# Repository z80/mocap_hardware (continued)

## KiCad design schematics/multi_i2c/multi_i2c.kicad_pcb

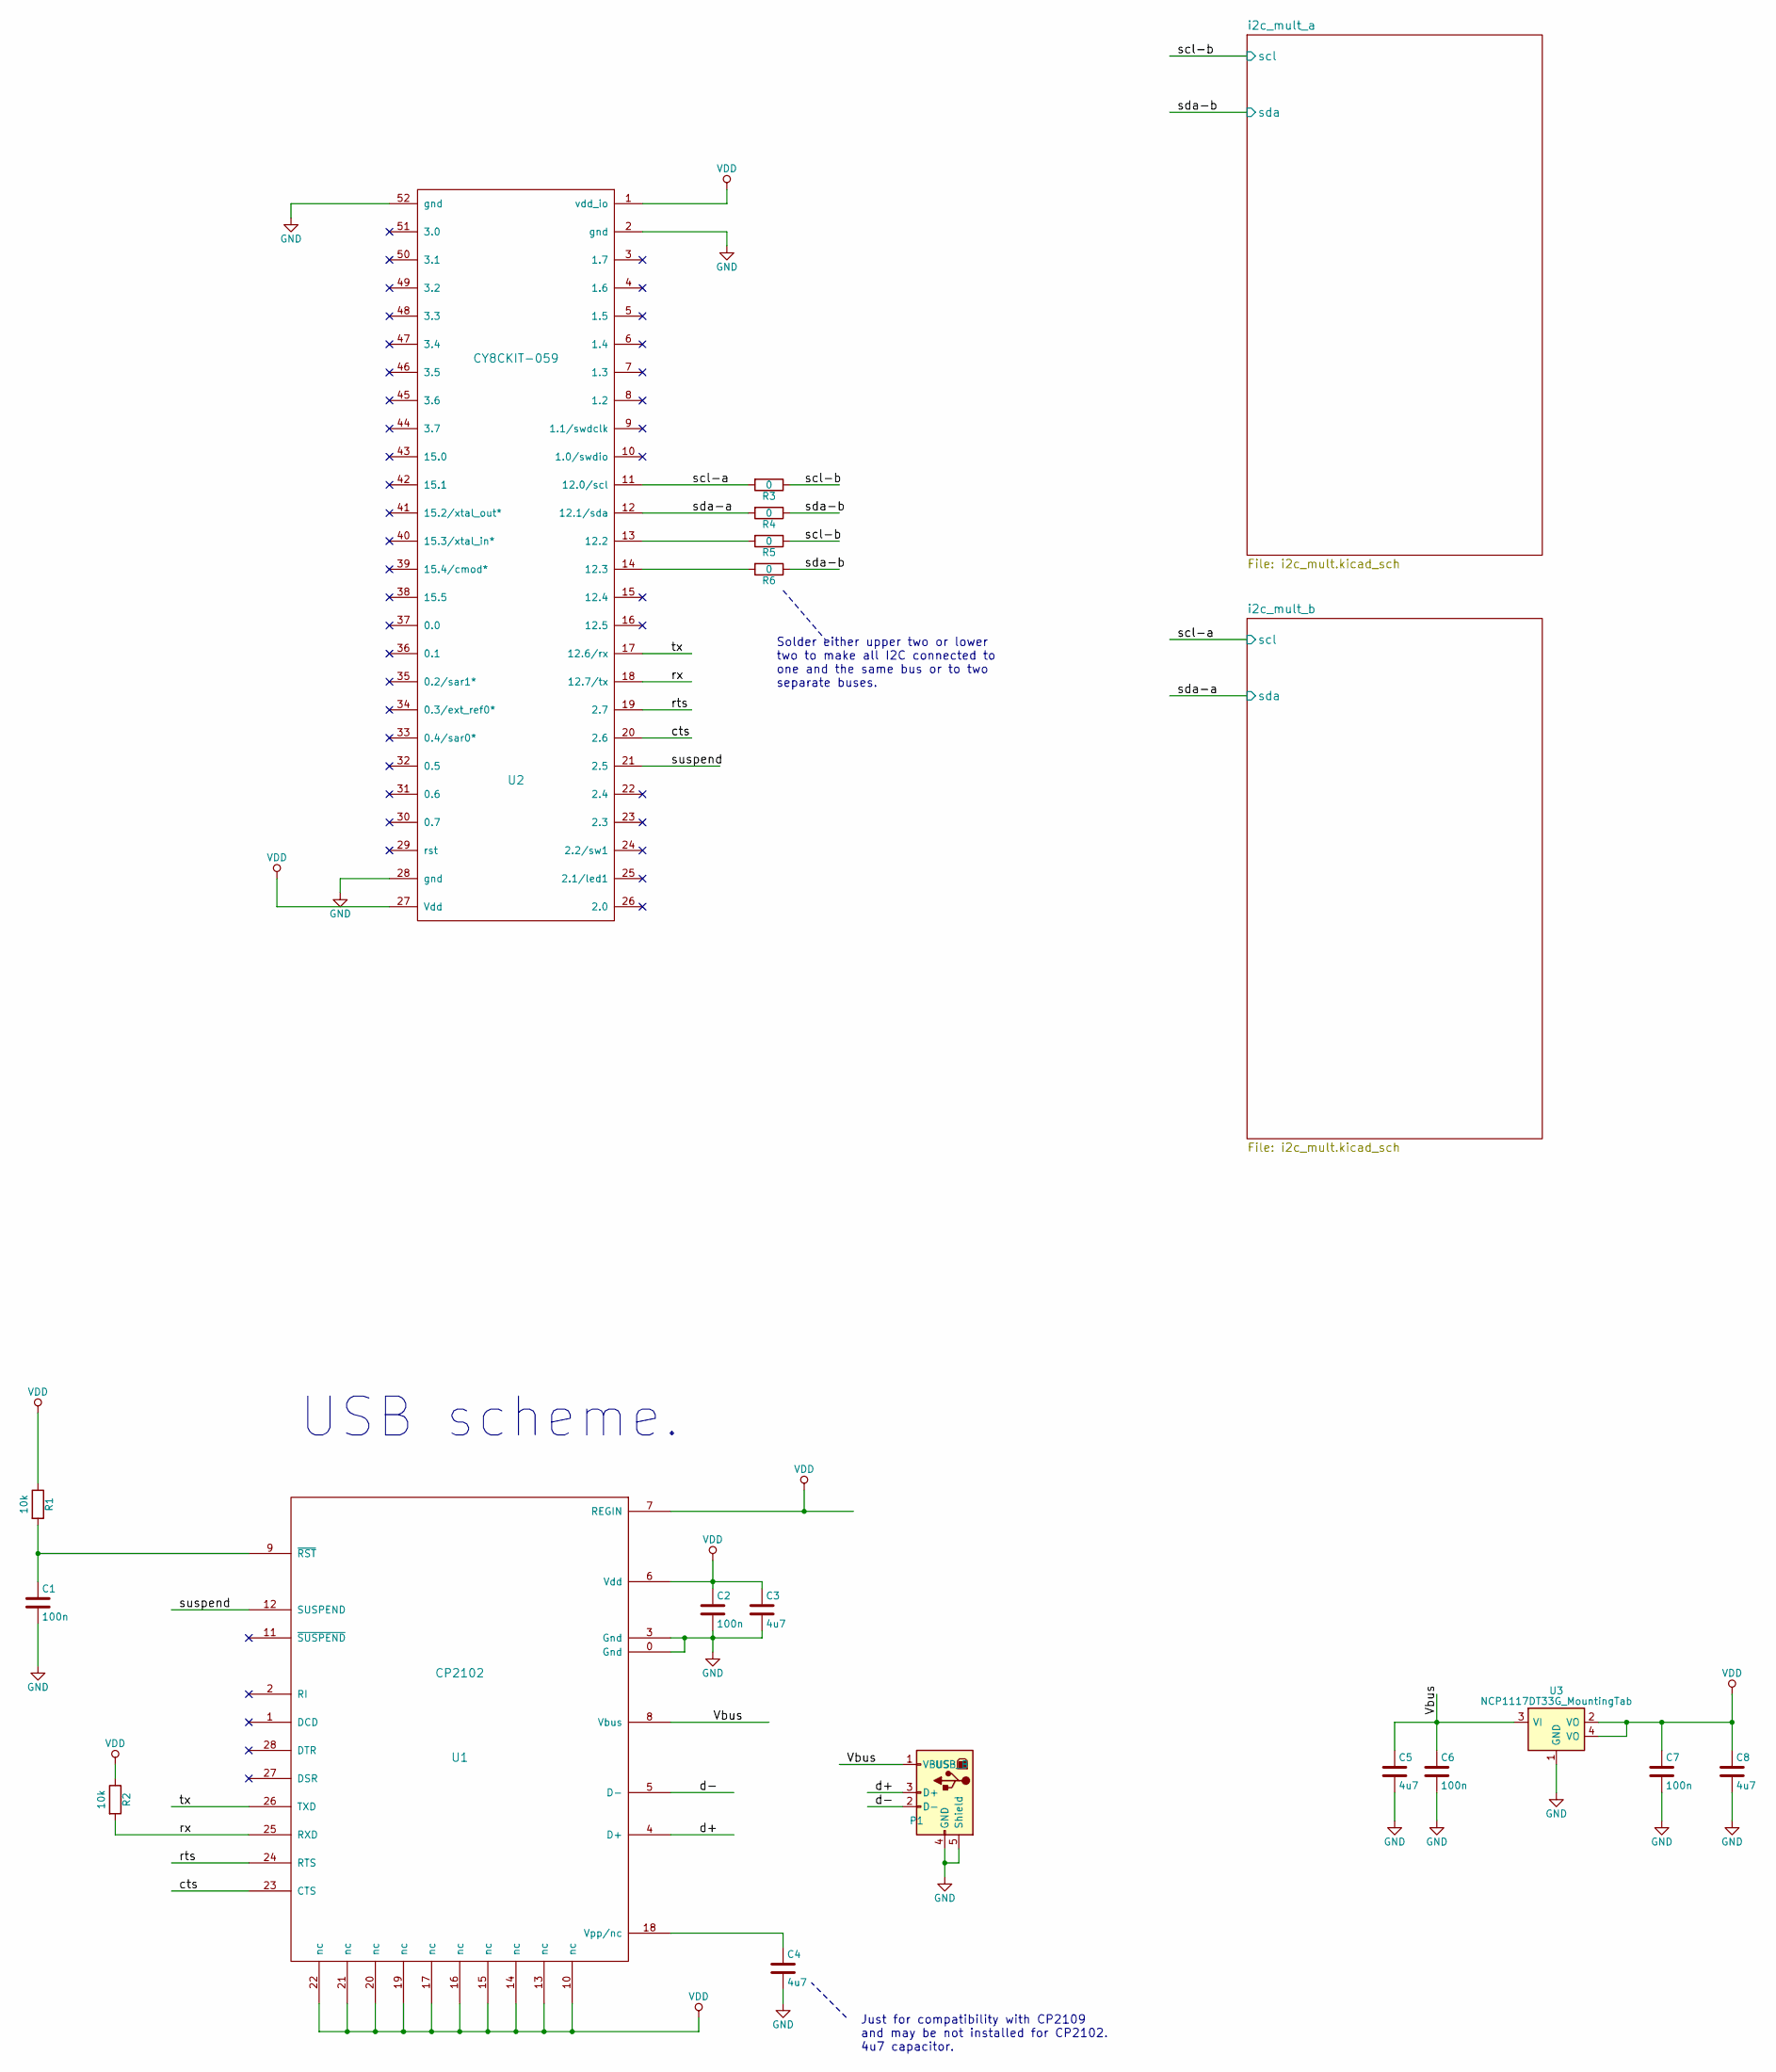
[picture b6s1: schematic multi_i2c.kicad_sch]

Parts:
C1, C2, C6, C7: 100n; C_0603
C3, C4, C5, C8: 4u7; C_0603
P1: USB_B
R1, R2: 10k; R_0603
R3, R4, R5, R6: 0; R_0603
U1: CP2102
U2: CY8CKIT-059; cy8ckit-059
U3: NCP1117DT33G_MountingTab; SOT-223

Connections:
/Vbus: C5.1, C6.1, P1.1 (VBUS), U1.8 (Vbus), U3.3 (VI)
/cts: U1.23 (CTS), U2.20 (2.6)
/d+: P1.3 (D+), U1.4 (D+)
/d-: P1.2 (D-), U1.5 (D-)
/rts: U1.24 (RTS), U2.19 (2.7)
/rx: R2.2, U1.25 (RXD), U2.18 (12.7/tx)
/scl-a: R3.2, U2.11 (12.0/scl); also elsewhere on the board
/scl-b: R3.1, R5.1; also elsewhere on the board
/sda-a: R4.2, U2.12 (12.1/sda); also elsewhere on the board
/sda-b: R4.1, R6.1; also elsewhere on the board
/suspend: U1.12 (SUSPEND), U2.21 (2.5)
/tx: U1.26 (TXD), U2.17 (12.6/rx)
GND: C1.2, C2.2, C3.2, C4.2, C5.2, C6.2, C7.2, C8.2, P1.4 (GND), P1.5 (Shield), U1.0 (Gnd), U1.3 (Gnd), U2.2 (gnd), U2.28 (gnd), U2.52 (gnd), U3.1 (GND); also elsewhere on the board
unnamed: C1.1, R1.2, U1.9 (~RST)
unnamed: C4.1, U1.18 (Vpp/nc)
unnamed: R5.2, U2.13 (12.2)
unnamed: R6.2, U2.14 (12.3)
VDD: C2.1, C3.1, C7.1, C8.1, R1.1, R2.1, U1.6 (Vdd), U1.7 (REGIN), U1.10 (nc), U1.13 (nc), U1.14 (nc), U1.15 (nc), U1.16 (nc), U1.17 (nc), U1.19 (nc), U1.20 (nc), U1.21 (nc), U1.22 (nc), U2.1 (vdd_io), U2.27 (Vdd), U3.2 (VO), U3.4 (VO); also elsewhere on the board

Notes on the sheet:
USB scheme.
Solder either upper two or lower two to make all I2C connected to one and the same bus or to two separate buses.
Just for compatibility with CP2109 and may be not installed for CP2102. 4u7 capacitor.

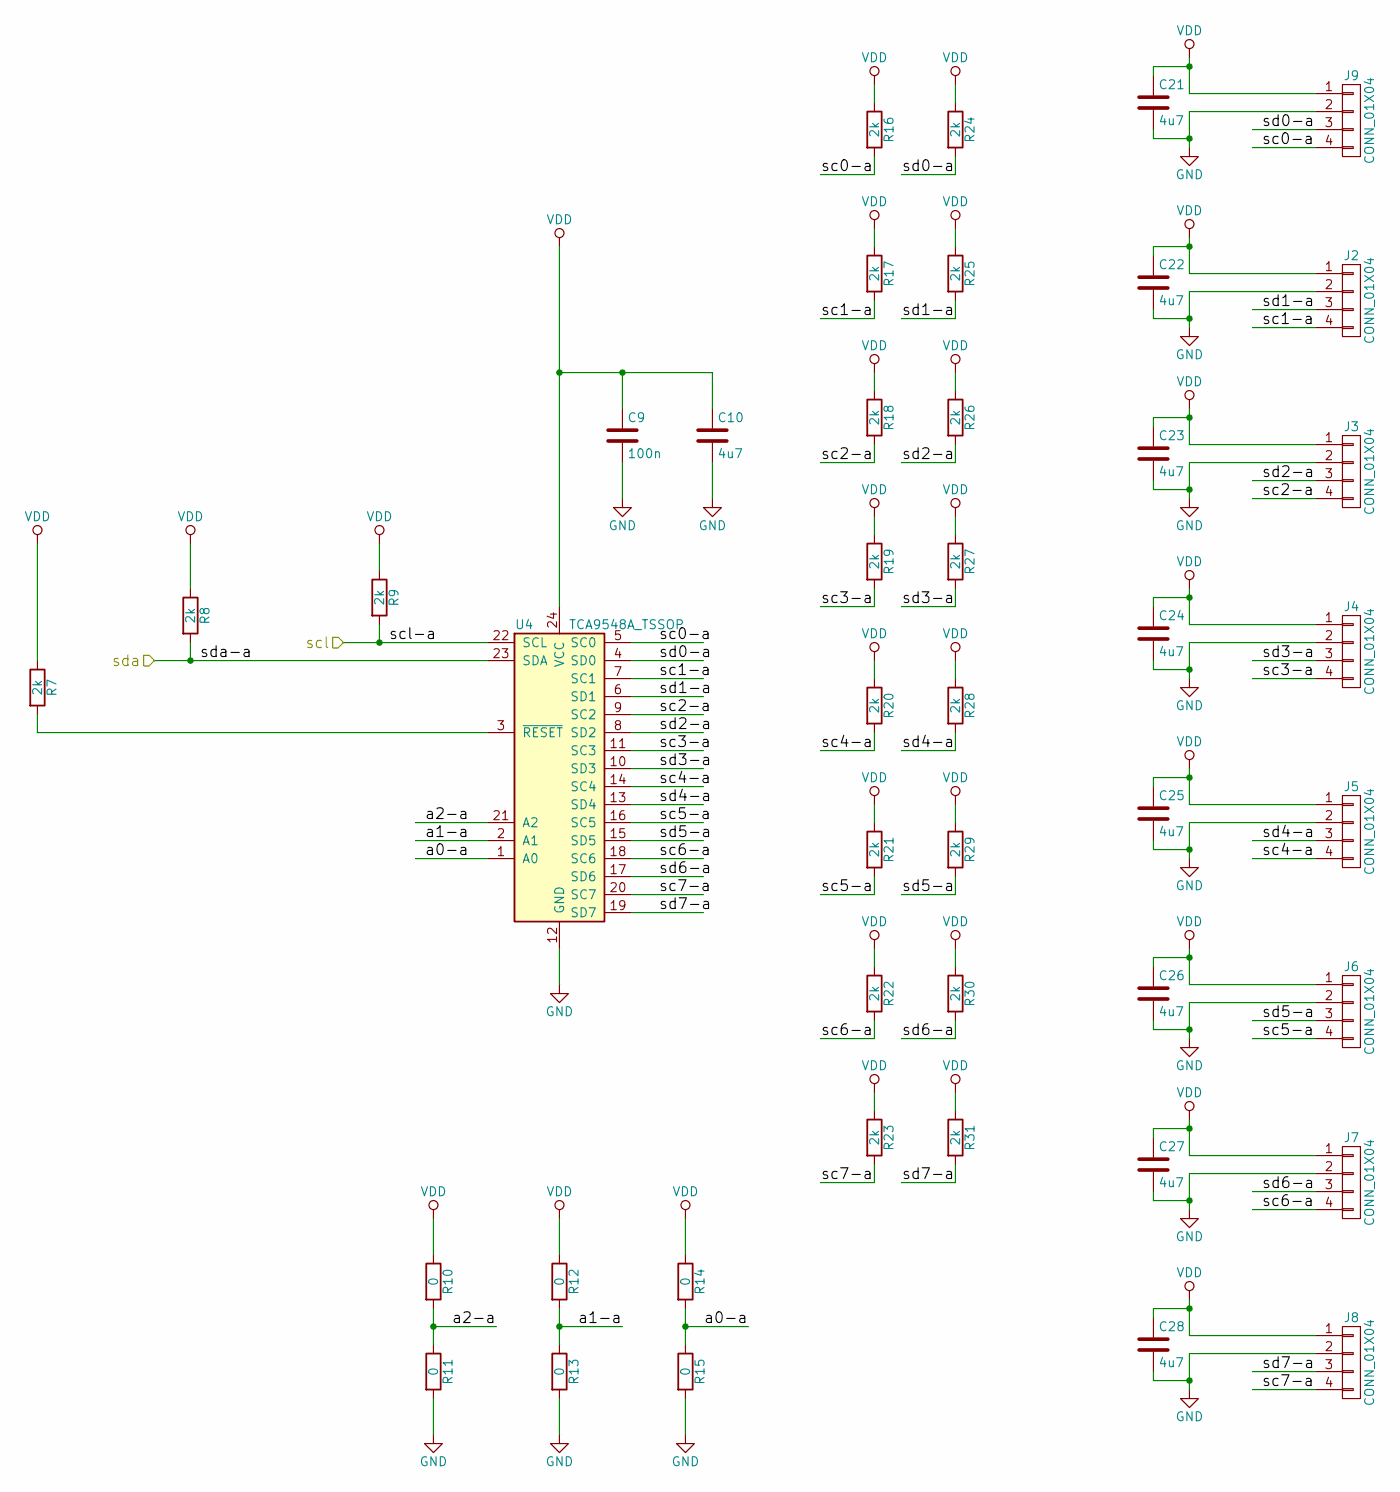
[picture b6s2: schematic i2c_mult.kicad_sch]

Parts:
C9: 100n; C_0603
C10, C21, C22, C23, C24, C25, C26, C27, C28: 4u7; C_0603
J2, J3, J4, J5, J6, J7, J8, J9: CONN_01X04; Pin_Header_Straight_1x04_Pitch1.27mm
R7, R8, R9, R16, R17, R18, R19, R20, R21, R22, R23, R24, R25, R26, R27, R28, R29, R30, R31: 2k; R_0603
R10, R11, R12, R13, R14, R15: 0; R_0603
U4: TCA9548A_TSSOP; TSSOP-24_4.4x7.8mm_Pitch0.65mm

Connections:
/i2c_mult_a/a0-a: R14.2, R15.1, U4.1 (A0)
/i2c_mult_a/a1-a: R12.2, R13.1, U4.2 (A1)
/i2c_mult_a/a2-a: R10.2, R11.1, U4.21 (A2)
/i2c_mult_a/sc1-a: J2.4, R17.2, U4.7 (SC1)
/i2c_mult_a/sc2-a: J3.4, R18.2, U4.9 (SC2)
/i2c_mult_a/sc3-a: J4.4, R19.2, U4.11 (SC3)
/i2c_mult_a/sc4-a: J5.4, R20.2, U4.14 (SC4)
/i2c_mult_a/sc5-a: J6.4, R21.2, U4.16 (SC5)
/i2c_mult_a/sc6-a: J7.4, R22.2, U4.18 (SC6)
/i2c_mult_a/sc7-a: J8.4, R23.2, U4.20 (SC7)
/i2c_mult_a/sd1-a: J2.3, R25.2, U4.6 (SD1)
/i2c_mult_a/sd2-a: J3.3, R26.2, U4.8 (SD2)
/i2c_mult_a/sd3-a: J4.3, R27.2, U4.10 (SD3)
/i2c_mult_a/sd4-a: J5.3, R28.2, U4.13 (SD4)
/i2c_mult_a/sd5-a: J6.3, R29.2, U4.15 (SD5)
/i2c_mult_a/sd6-a: J7.3, R30.2, U4.17 (SD6)
/i2c_mult_a/sd7-a: J8.3, R31.2, U4.19 (SD7)
/scl-b: R9.2, U4.22 (SCL); also elsewhere on the board
/sda-b: R8.2, U4.23 (SDA); also elsewhere on the board
GND: C9.2, C10.2, C21.2, C22.2, C23.2, C24.2, C25.2, C26.2, C27.2, C28.2, J2.2, J3.2, J4.2, J5.2, J6.2, J7.2, J8.2, J9.2, R11.2, R13.2, R15.2, U4.12 (GND); also elsewhere on the board
unnamed: R7.2, U4.3 (~RESET)
VDD: C9.1, C10.1, C21.1, C22.1, C23.1, C24.1, C25.1, C26.1, C27.1, C28.1, J2.1, J3.1, J4.1, J5.1, J6.1, J7.1, J8.1, J9.1, R7.1, R8.1, R9.1, R10.1, R12.1, R14.1, R16.1, R17.1, R18.1, R19.1, R20.1, R21.1, R22.1, R23.1, R24.1, R25.1, R26.1, R27.1, R28.1, R29.1, R30.1, R31.1, U4.24 (VCC); also elsewhere on the board

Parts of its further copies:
C11: 100n; C_0603
C12, C13, C14, C15, C16, C17, C18, C19, C20: 4u7; C_0603
J1, J10, J11, J12, J13, J14, J15, J16: CONN_01X04; Pin_Header_Straight_1x04_Pitch1.27mm
R32, R33, R34, R41, R42, R43, R44, R45, R46, R47, R48, R49, R50, R51, R52, R53, R54, R55, R56: 2k; R_0603
R35, R36, R37, R38, R39, R40: 0; R_0603
U5: TCA9548A_TSSOP; TSSOP-24_4.4x7.8mm_Pitch0.65mm

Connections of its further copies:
/i2c_mult_b/a0-a: R39.2, R40.1, U5.1 (A0)
/i2c_mult_b/a1-a: R37.2, R38.1, U5.2 (A1)
/i2c_mult_b/a2-a: R35.2, R36.1, U5.21 (A2)
/i2c_mult_b/sc1-a: J10.4, R42.2, U5.7 (SC1)
/i2c_mult_b/sc2-a: J11.4, R43.2, U5.9 (SC2)
/i2c_mult_b/sc3-a: J12.4, R44.2, U5.11 (SC3)
/i2c_mult_b/sc4-a: J13.4, R45.2, U5.14 (SC4)
/i2c_mult_b/sc5-a: J14.4, R46.2, U5.16 (SC5)
/i2c_mult_b/sc6-a: J15.4, R47.2, U5.18 (SC6)
/i2c_mult_b/sc7-a: J16.4, R48.2, U5.20 (SC7)
/i2c_mult_b/sd1-a: J10.3, R50.2, U5.6 (SD1)
/i2c_mult_b/sd2-a: J11.3, R51.2, U5.8 (SD2)
/i2c_mult_b/sd3-a: J12.3, R52.2, U5.10 (SD3)
/i2c_mult_b/sd4-a: J13.3, R53.2, U5.13 (SD4)
/i2c_mult_b/sd5-a: J14.3, R54.2, U5.15 (SD5)
/i2c_mult_b/sd6-a: J15.3, R55.2, U5.17 (SD6)
/i2c_mult_b/sd7-a: J16.3, R56.2, U5.19 (SD7)
/scl-a: R34.2, U5.22 (SCL); also elsewhere on the board
/sda-a: R33.2, U5.23 (SDA); also elsewhere on the board
GND: C11.2, C12.2, C13.2, C14.2, C15.2, C16.2, C17.2, C18.2, C19.2, C20.2, J1.2, J10.2, J11.2, J12.2, J13.2, J14.2, J15.2, J16.2, R36.2, R38.2, R40.2, U5.12 (GND); also elsewhere on the board
unnamed: R32.2, U5.3 (~RESET)
VDD: C11.1, C12.1, C13.1, C14.1, C15.1, C16.1, C17.1, C18.1, C19.1, C20.1, J1.1, J10.1, J11.1, J12.1, J13.1, J14.1, J15.1, J16.1, R32.1, R33.1, R34.1, R35.1, R37.1, R39.1, R41.1, R42.1, R43.1, R44.1, R45.1, R46.1, R47.1, R48.1, R49.1, R50.1, R51.1, R52.1, R53.1, R54.1, R55.1, R56.1, U5.24 (VCC); also elsewhere on the board

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
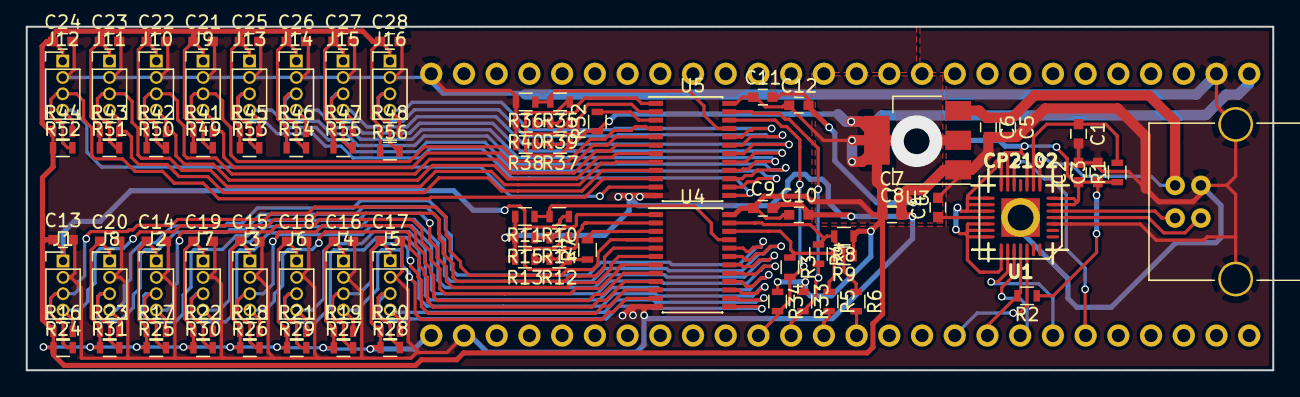
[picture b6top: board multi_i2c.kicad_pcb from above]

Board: 2 copper layers, 96.8 x 26.7 mm, 106 parts (1 on the bottom side), 58 nets.

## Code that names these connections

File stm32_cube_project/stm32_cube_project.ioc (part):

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Mcu.Name=STM32F405RGTx
Mcu.Package=LQFP64
Mcu.UserName=STM32F405RGTx
PA0-WKUP.Signal=ADCx_IN0
PA1.GPIOParameters=GPIO_Label
PA1.GPIO_Label=BATT_CHARGE_EN
PA1.Signal=GPIO_Output
PA10.Mode=Asynchronous
PA10.Signal=USART1_RX
PA11.Mode=Device_Only
PA11.Signal=USB_OTG_FS_DM
PA12.Mode=Device_Only
PA12.Signal=USB_OTG_FS_DP
PA13.Mode=Serial_Wire
PA13.Signal=SYS_JTMS-SWDIO
PA14.Mode=Serial_Wire
PA14.Signal=SYS_JTCK-SWCLK
PA2.Mode=Asynchronous
PA2.Signal=USART2_TX
PA3.Mode=Asynchronous
PA3.Signal=USART2_RX
PA5.GPIOParameters=GPIO_Label
PA5.GPIO_Label=LED_0
PA5.Signal=GPIO_Output
PA6.GPIOParameters=GPIO_Label
PA6.GPIO_Label=LED_1
PA6.Signal=GPIO_Output
PA7.GPIOParameters=GPIO_Label
PA7.GPIO_Label=LED_2
PA7.Signal=GPIO_Output
PA8.Mode=I2C
PA8.Signal=I2C3_SCL
PA9.Mode=Asynchronous
PA9.Signal=USART1_TX
PB10.Mode=I2C
PB10.Signal=I2C2_SCL
PB11.Mode=I2C
PB11.Signal=I2C2_SDA
PB12.GPIOParameters=GPIO_Label
PB12.GPIO_Label=BATT_CHARGE_EN
PB12.Signal=GPIO_Output
PB6.Mode=I2C
PB6.Signal=I2C1_SCL
PB7.Mode=I2C
PB7.Signal=I2C1_SDA
PC9.Mode=I2C
PC9.Signal=I2C3_SDA
PH0-OSC_IN.Mode=HSE-External-Oscillator
PH0-OSC_IN.Signal=RCC_OSC_IN
PH1-OSC_OUT.Mode=HSE-External-Oscillator
PH1-OSC_OUT.Signal=RCC_OSC_OUT
RCC.HSE_VALUE=8000000
RCC.SYSCLKFreq_VALUE=72000000
RCC.SYSCLKSource=RCC_SYSCLKSOURCE_PLLCLK
board=custom

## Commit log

2024-03-15 Put all in.
2024-03-17 I think it is finished.
2024-03-17 Shift registers capable of wirking with TTL logic. Need the one which is both serial and parallel to be able to chain them in series.
2024-03-21 i2c multiplexer.
2024-03-21 Added resistor to the interrupt signal.
2024-03-31 Making the host board for multiple sensors.
2024-03-31 4 shift registers are added.
2024-03-31 Added battery charger.
2024-03-31 Replaced linear regulator with fixed 3.3V Buck converter MCP1603.
2024-03-31 Inserted ESP-12S WIFI module.
2024-03-31 Added stm32f405rgt6.
2024-03-31 Selarated INT, SCL and SDA lines with GND and VDD so that crosstalk is reduced
2024-03-31 Generated STM32 project. May change pins later.
2024-04-04 Cannot re-save stm32f405rgt6. May be need to copy it again from the other project.
2024-04-07 Fixed STM MCU symbol.
2024-04-08 Added two 27 pin sockets.
2024-04-08 Added all 5 sockets.
2024-04-08 Microchip BLE module BM70 or BM71.
2024-04-08 No errors, no warnings.
2024-04-10 Replaced ESP-21S with BM71 Microchip UART BLE module.
2024-04-11 Added power monitor. Split grounding and signals across ethernet cable twisted pairs.
2024-04-14 Assigned footprints. Also, just in case found a chip I2C to diff. pair.
2024-04-14 Assigning URLs.
2024-04-14 Assigning URLs...
2024-04-14 Version with x4 RJ45 sockets. But probably it is not the best idea because there is just one instance of this x4 socker cheaper than 4 single ones.
2024-04-14 Revert "Version with x4 RJ45 sockets. But probably it is not the best idea because"
    This reverts commit d093a493317f39921dd6a9879e5a0815c2525c06.
2024-04-14 Assigned RJ45 URL and footprint.
2024-04-18 Placing footprints...
2024-04-18 RJ45 socket.
2024-04-21 Placing components...
2024-04-21 Placing components, tracing wires.
2024-04-25 Tracing...
2024-04-28 Finished. But it is too sparse. Probably can make it x2 more dense.
2024-04-28 Moving footprints...
2024-05-03 Prepared to move the MCU.
2024-05-05 Making wires thicker... Added Gnd zone.
2024-05-05 Probably good enough...
2024-09-03 STM datasheet.
2024-09-03 BM71 configuration software.
2024-09-05 Older tools.
2024-09-05 BoM.
2024-09-05 The STM32 firmware builds now. The key was to delete the project from the workspace and go via "file->import".
2024-09-06 Added bno055 support from the old project. Doesn't compile now.
2024-09-07 Compiles.
2024-09-07 One test BNO055 initializes when plugged in. Also, LED task for some reason breaks if LED initialized before IMU. So put LED task after IMU task.
2024-09-08 uart_service.py at least runs. It opens the device and at least says that it sends the data.
2024-09-08 Command parsing.
2024-09-08 Committed all files.
2024-09-08 Added UART task to the main.
2024-09-09 Debugging command reception. Currently receiving commands doesn't quite work. Will tru interrupt-based UART routine.
2024-09-10 All the files.
2024-09-10 Trying to ignore unnecessary files.
2024-09-11 No need in the large buffer. Can just send data as it goes.
2024-09-11 Making the data service app...
2024-09-12 Runs and returns quaternions.
2024-09-13 Also added ADC battery voltage readings in the very beginning of the packet.
2024-09-13 Also report battry voltage.
2024-09-18 Adding actual streaming functionality.
2024-09-18 Sending data works.
2024-09-18 Keep data in the dictionary.
2024-09-28 BMI085.
2024-09-28 Making a BMI085 board.
2024-10-15 The BMI085 board has a bug. Pin 7 is not connected to Vdd. When fixed by soldering a wire on top to the nearest Vdd pin on a filtering capacitor, it starts working. Also, I2C addresses should be mult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
2024-10-15 Accelerometer works after adding software reset in the beginning of the initialization routine.
2024-10-15 I2C 400kHz.
2024-10-15 Sensor configuration. Will need to improve it in the future.
2024-10-15 With channel switches Full cycle of 1) switching I2C channel, 2) reading acceleromenter, 3) reading gyroscope takes slightly under 500us.
2024-10-16 Copied over Magdwick algorithm.
2024-10-18 The algorithm itself works. But the orientation drifts. Need to compensate for the bias.
2024-10-18 Added bias estimation and made sure it actually engages when IMU is idle on a table.
2024-10-21 Implemented IRQ-based data acquisition.
2024-10-22 Debugging...
2024-10-23 Just put everything under version control.
2024-10-23 Delay doesn't work outside of stasks. And that seem to be the problem I had for two days.
2024-10-23 And this way the initialization always works. May be the issue was in memory allocation??? Too large structure declared???
2024-10-24 So far initializes every time.
2024-10-24 Should have enabled I2C interrupts. Data acquisition and AHRS algorithm work.
2024-10-26 Value as uint32_t.
2024-10-26 Added discrete quaternion representation for sending over UART. Returned back the UART task. But removed mode switches as BMI085 is IMU-only. There is no magnetometer.
2024-10-26 It seems, it works as intended byt the UART data rate is too slow to push through all the data. Need to speed it up...
2024-10-27 Sometimes the data is shifted. Need to figure out what exactly is going on. Due to that quaternions are weired. CRC8 fixes the problem but the frame is dropped.
2024-10-27 Sending only measured IMUs.
2024-10-28 Re-done the sensor board. Now it can be up 4 sensors on a single cable.
2024-10-28 Little tail is not needed.
2024-10-30 Slightly re-routed wires so that through power and ground do not go through the IMU chip. Instead, they go around.
2024-10-30 Removed a tiny tail.
2024-10-30 Byte-based data exchange. If still not enough, I potentially can not transmit q.w but only its sign instead as magnitude can be derived from other 3 numbers.
2024-10-30 Commented out constant output.
2024-11-24 Changed I2C duty cycle. Aslo, with long wires sensors hang up. Added 4u7 capacitors on top of 100n ones. That seem to helped.
2024-12-04 Added wires.
2024-12-04 More resolution.
2024-12-04 Another cutout and edge creases.
2024-12-04 Half editing done, probably.
2024-12-04 Created the other half as a reference to the first one. Because of that they are edited simultaneously.
2024-12-04 Added tabs.
2024-12-05 Made remeshed versions for 3d printing.
2024-12-05 Applied boolean. Without it walls still exist.
2024-12-07 Added tabs. Made walls around wire holes thicker.
2024-12-31 Before converting curves to meshes.
2024-12-31 Added outer surface for the cable exit.
2024-12-31 Before merging and boolean operations.
2024-12-31 After cutting.
2025-01-03 Reverted, increased cable cutout vertical size. Also added screw holes.
2025-01-03 Moved screw cutouts to the correct group.
2025-01-03 After joining and booleans.
2025-01-08 Don't need this delay anymore.
2025-01-08 This is the reason why on one slot it caused failure.
2025-01-08 Compiled firmware.
2025-01-10 Finger piece design.
2025-01-11 The utility tool for BM71.
2025-01-11 Unreal plugin source code.
2025-01-11 Made all fingers.
2025-01-13 Changed dimensions for pinky and thumb adapters.
2025-01-15 Palm piece.
2025-01-17 Made it thinner.
2025-01-19 Moved IMU case to a dedicated folder.
2025-01-20 Made combined meshes.
2025-01-21 Added separate left and right palm pieces.
2025-01-26 Rigid edges.
2025-02-23 Started foot holder.
2025-02-23 Foot and toe holders.
2025-03-07 increased size
2025-03-11 Left versions.
2025-03-31 For some reason timer toesn't work inside coroutines. But just message counting works.
2025-03-31 Just saving everything.
2025-03-31 Another inner loop to prevent all_data growing.
2025-04-30 Starting script so that I don't have to manually initialize the virtual environment.
2025-06-23 Redoing the schematic.
2025-06-23 Changing the schematic.
2025-06-24 Making changes...
2025-06-24 3 I2C bus, adding capacitors to sensor power lines...
2025-06-24 Configuring the MCU.
2025-06-24 All I2C multiplexers have the same address selection pins configuration. Added 22u capacitors.
2025-06-25 Removing old wires.
2025-06-25 Upgraded to KiCad9.0.
2025-06-26 Replaced buck with low drop linear for the bluetooth.
2025-06-26 Groupping different logical component groups to move them together.
2025-06-30 I think, I've finished it.
2025-06-30 A script to move all values to silkscreen layer.
2025-06-30 A ground with vias as recommended by the BM71 manual.
2025-07-01 Adjusted the batt_charge_en pin position. Added extra vias for smaller resistance.
